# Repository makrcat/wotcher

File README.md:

## wotcher

wotcher is a digital raise-to-wake LED watch, with 89 LEDs in total! It uses something called charlieplexing to make all the lights glow at once. 

## circuit design
Charlieplexing is a method to limit current & control many LED's with only a couple of microcontroller pins, by switching between LEDs really fast so it looks like they're always on, due to the phenomenon of persistence of vision.

- My project uses a charlieplexing chip (IS31FL3731-QF) to drive the 7-segment display & all 60 LEDs, which is 88 LEDs in total. 
- The clock chip (DS3231MZ+) is necessary here because the ATtiny's internal RC oscillator clock is terrible at time keeping. The clock chip only drifts like 2 seconds a year! So that's cool.
- I'm also including an accelerometer so that it's raise-to-wake, like those Apple watches.

# some inspiration

It's inspired by various retro-style watches, such as the aptly named retrowatch, the charlie watch, and the decko circuit face watch, as well as other pinterest pictures.

<i>from left to right, <a src="https://trmm.net/Charliewatch/">charliewatch</a>, <a src="https://github.com/RafaelRiber/RetroWatch">retrowatch</a>, decko (by the Terminelectro company)</i>

## features

I'm going to use embedded c++ to code this later, when I get my breadboard components.

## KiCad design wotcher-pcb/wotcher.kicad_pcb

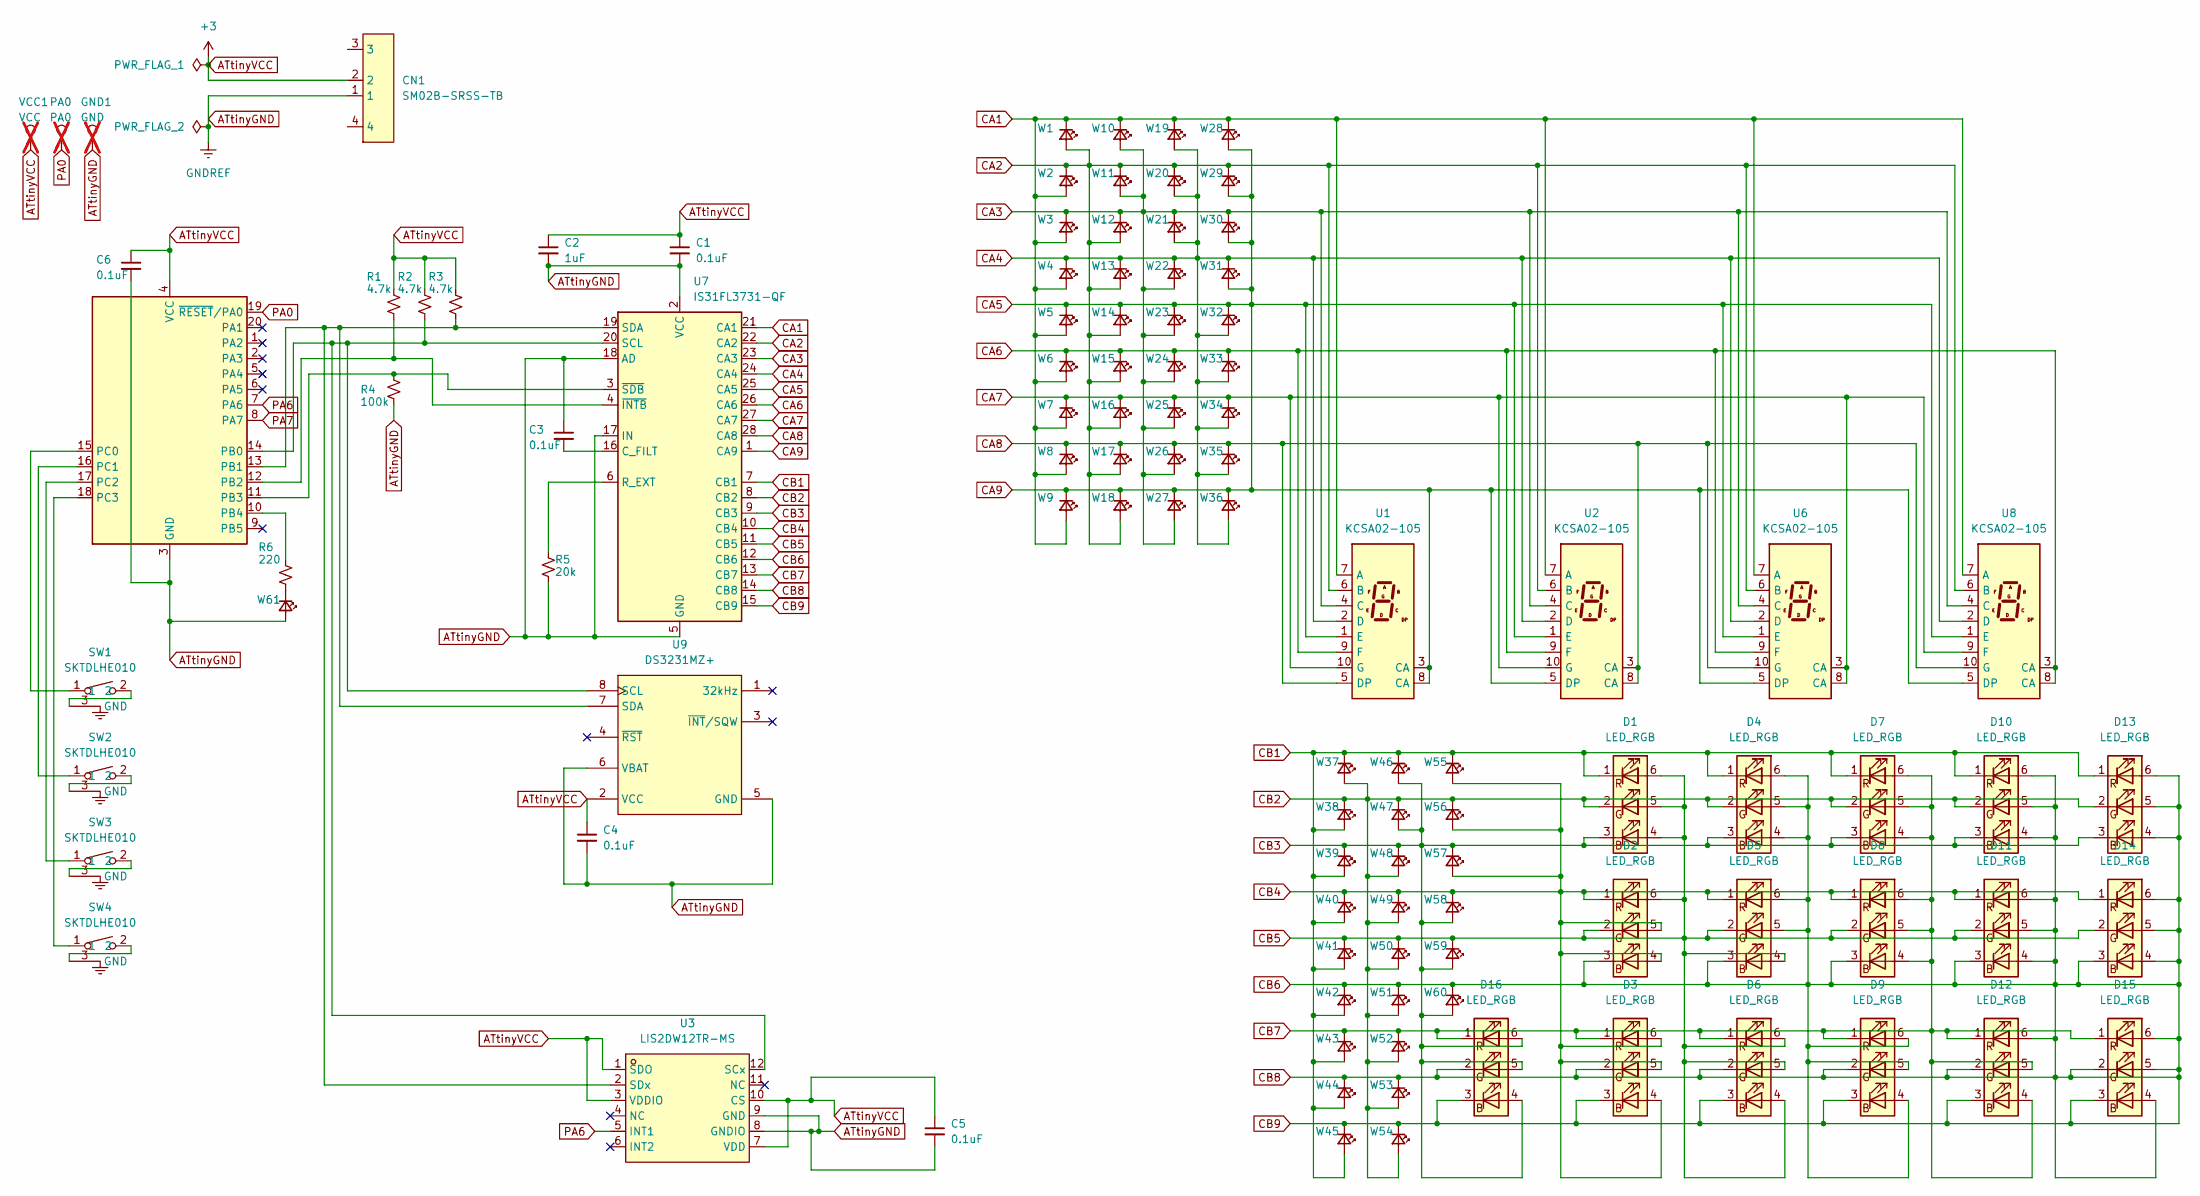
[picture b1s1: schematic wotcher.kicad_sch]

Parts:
C1, C3, C4, C5, C6: 0.1uF; C_01005_0402Metric
C2: 1uF; C_01005_0402Metric
CN1: SM02B-SRSS-TB; CONN-SMD_2P-P1.00_SM02B-SRSS-TB-LF-SN; MPN SM02B-SRSS-TB(LF)(SN); LCSC Part C160402
D1, D2, D3, D4, D5, D6, D7, D8, D9, D10, D11, D12, D13, D14, D15, D16: LED_RGB; LED-ARRAY-SMD_6P-L1.6-W1.6-TL_19-337C-RSBHGHC-M01
GND1: GND; TestPoint_Pad_D1.5mm; not fitted
PA0: PA0; TestPoint_Pad_D1.5mm; not fitted
R1, R2, R3: 4.7k; R_0201_0603Metric
R4: 100k; R_0201_0603Metric
R5: 20k; R_0201_0603Metric
R6: 220; R_0201_0603Metric
SW1, SW2, SW3, SW4: SKTDLHE010; KEY-SMD_SKTDLHE010; MPN SKTDLHE010; LCSC Part C380198
U1, U2, U6, U8: KCSA02-105; KCSC02-105
U3: LIS2DW12TR-MS; LGA-12_L2.0-W2.0_BMA250; MPN LIS2DW12TR-MS; LCSC Part C50385411
U5: ATtiny1616-M; QFN-20_L3.0-W3.0-P0.40-BL-EP1.7
U7: IS31FL3731-QF; QFN-28_L4.0-W4.0-P0.40-BL-EP
U9: DS3231MZ+; SOIC-8_L4.9-W3.9-P1.27-LS6.0-BL; MPN DS3231MZ+TRL; LCSC Part C107410
VCC1: VCC; TestPoint_Pad_D1.5mm; not fitted
W1, W2, W3, W4, W5, W6, W7, W8, W9, W10, W11, W12, W13, W14, W15, W16, W17, W18, W19, W20, W21, W22, W23, W24, W25, W26, W27, W28, W29, W30, W31, W32, W33, W34, W35, W36, W37, W38, W39, W40, W41, W42, W43, W44, W45, W46, W47, W48, W49, W50, W51, W52, W53, W54, W55, W56, W57, W58, W59, W60, W61: LED_Small; LED-SMD_L1.6-W0.8-R-RD

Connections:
ATtinyGND: C1.2, C2.2, C3.1, C4.2, C5.2, C6.2, CN1.1, GND1.1, R4.2, R5.2, U3.8 (GNDIO), U3.9 (GND), U5.3 (GND), U5.21 (GND), U7.2 (VCC), U7.5 (GND), U7.17 (IN), U7.18 (AD), U7.29 (GND), U9.5 (GND), U9.6 (VBAT), W61.2 (A)
ATtinyVCC: C1.1, C2.1, C4.1, C5.1, C6.1, CN1.2, R1.1, R2.1, R3.1, U3.1 (SDO), U3.3 (VDDIO), U3.7 (VDD), U3.10 (CS), U5.4 (VCC), U9.2 (VCC), VCC1.1
CA1: U1.7 (A), U2.7 (A), U6.7 (A), U7.21 (CA1), U8.7 (A), W1.1 (K), W2.2 (A), W3.2 (A), W4.2 (A), W5.2 (A), W6.2 (A), W7.2 (A), W8.2 (A), W9.2 (A), W10.1 (K), W19.1 (K), W28.1 (K)
CA2: U1.6 (B), U2.6 (B), U6.6 (B), U7.22 (CA2), U8.6 (B), W1.2 (A), W2.1 (K), W11.1 (K), W12.2 (A), W13.2 (A), W14.2 (A), W15.2 (A), W16.2 (A), W17.2 (A), W18.2 (A), W20.1 (K), W29.1 (K)
CA3: U1.4 (C), U2.4 (C), U6.4 (C), U7.23 (CA3), U8.4 (C), W3.1 (K), W10.2 (A), W11.2 (A), W12.1 (K), W21.1 (K), W22.2 (A), W23.2 (A), W24.2 (A), W25.2 (A), W26.2 (A), W27.2 (A), W30.1 (K)
CA4: U1.2 (D), U2.2 (D), U6.2 (D), U7.24 (CA4), U8.2 (D), W4.1 (K), W13.1 (K), W19.2 (A), W20.2 (A), W21.2 (A), W22.1 (K), W31.1 (K), W32.2 (A), W33.2 (A), W34.2 (A), W35.2 (A), W36.2 (A)
CA5: U1.1 (E), U1.3 (CA), U1.8 (CA), U2.1 (E), U2.5 (DP), U6.1 (E), U6.5 (DP), U7.1 (CA9), U7.25 (CA5), U8.1 (E), U8.5 (DP), W5.1 (K), W9.1 (K), W14.1 (K), W18.1 (K), W23.1 (K), W27.1 (K), W28.2 (A), W29.2 (A), W30.2 (A), W31.2 (A), W32.1 (K), W36.1 (K)
CA6: U1.9 (F), U2.9 (F), U6.9 (F), U7.26 (CA6), U8.3 (CA), U8.8 (CA), W6.1 (K), W15.1 (K), W24.1 (K), W33.1 (K)
CA7: U1.10 (G), U2.10 (G), U6.3 (CA), U6.8 (CA), U7.27 (CA7), U8.9 (F), W7.1 (K), W16.1 (K), W25.1 (K), W34.1 (K)
CA8: U1.5 (DP), U2.3 (CA), U2.8 (CA), U6.10 (G), U7.28 (CA8), U8.10 (G), W8.1 (K), W17.1 (K), W26.1 (K), W35.1 (K)
CB1: D1.1 (RK), D4.1 (RK), D7.1 (RK), D10.1 (RK), D13.1 (RK), U7.7 (CB1), W37.1 (K), W38.2 (A), W39.2 (A), W40.2 (A), W41.2 (A), W42.2 (A), W43.2 (A), W44.2 (A), W45.2 (A), W46.1 (K), W55.1 (K)
CB2: D1.2 (GK), D4.2 (GK), D7.2 (GK), D10.2 (GK), D13.2 (GK), U7.8 (CB2), W37.2 (A), W38.1 (K), W47.1 (K), W48.2 (A), W49.2 (A), W50.2 (A), W51.2 (A), W52.2 (A), W53.2 (A), W54.2 (A), W56.1 (K)
CB3: D1.3 (BK), D4.3 (BK), D7.3 (BK), D10.3 (BK), D13.3 (BK), D16.4 (BA), D16.5 (GA), D16.6 (RA), U7.9 (CB3), W39.1 (K), W46.2 (A), W47.2 (A), W48.1 (K), W57.1 (K), W58.2 (A), W59.2 (A), W60.2 (A)
CB4: D2.1 (RK), D2.4 (BA), D2.5 (GA), D3.4 (BA), D3.5 (GA), D3.6 (RA), D5.1 (RK), D8.1 (RK), D11.1 (RK), D14.1 (RK), U7.10 (CB4), W40.1 (K), W49.1 (K), W55.2 (A), W56.2 (A), W57.2 (A), W58.1 (K)
CB5: D1.4 (BA), D1.5 (GA), D1.6 (RA), D2.2 (GK), D2.6 (RA), D5.2 (GK), D5.4 (BA), D6.4 (BA), D6.5 (GA), D6.6 (RA), D8.2 (GK), D11.2 (GK), D14.2 (GK), U7.11 (CB5), W41.1 (K), W50.1 (K), W59.1 (K)
CB6: D2.3 (BK), D3.2 (GK), D3.3 (BK), D4.4 (BA), D4.5 (GA), D4.6 (RA), D5.3 (BK), D5.5 (GA), D5.6 (RA), D6.2 (GK), D6.3 (BK), D8.3 (BK), D9.2 (GK), D9.3 (BK), D9.4 (BA), D9.5 (GA), D9.6 (RA), D10.4 (BA), D10.5 (GA), D10.6 (RA), D11.3 (BK), D11.4 (BA), D11.5 (GA), D11.6 (RA), D12.2 (GK), D12.3 (BK), D12.6 (RA), D13.4 (BA), D13.5 (GA), D13.6 (RA), D14.3 (BK), D14.4 (BA), D14.5 (GA), D14.6 (RA), D15.2 (GK), D15.3 (BK), D15.4 (BA), D15.5 (GA), D15.6 (RA), D16.2 (GK), D16.3 (BK), U7.12 (CB6), U7.14 (CB8), U7.15 (CB9), W42.1 (K), W44.1 (K), W45.1 (K), W51.1 (K), W53.1 (K), W54.1 (K), W60.1 (K)
CB7: D3.1 (RK), D6.1 (RK), D7.4 (BA), D7.5 (GA), D7.6 (RA), D8.4 (BA), D8.5 (GA), D8.6 (RA), D9.1 (RK), D12.1 (RK), D12.4 (BA), D12.5 (GA), D15.1 (RK), D16.1 (RK), U7.13 (CB7), W43.1 (K), W52.1 (K)
unnamed: SW1.2, SW1.3 (GND)
unnamed: SW2.2, SW2.3 (GND)
unnamed: SW3.2, SW3.3 (GND)
unnamed: SW4.2, SW4.3 (GND)
unnamed: R2.2, U3.12 (SCx), U5.14 (PB0), U7.20 (SCL), U9.8 (SCL)
unnamed: R3.2, U3.2 (SDx), U5.13 (PB1), U7.19 (SDA), U9.7 (SDA)
unnamed: R1.2, U5.12 (PB2), U7.4 (~INTB)
unnamed: R4.1, U5.11 (PB3), U7.3 (~SDB)
unnamed: R6.1, U5.10 (PB4)
unnamed: SW1.1, U5.15 (PC0)
unnamed: SW2.1, U5.16 (PC1)
unnamed: SW3.1, U5.17 (PC2)
unnamed: SW4.1, U5.18 (PC3)
unnamed: C3.2, U7.16 (C_FILT)
unnamed: R5.1, U7.6 (R_EXT)
unnamed: R6.2, W61.1 (K)
PA0: PA0.1, U5.19 (~RESET/PA0)
PA6: U3.5 (INT1), U5.7 (PA6)
PA7: U5.8 (PA7)

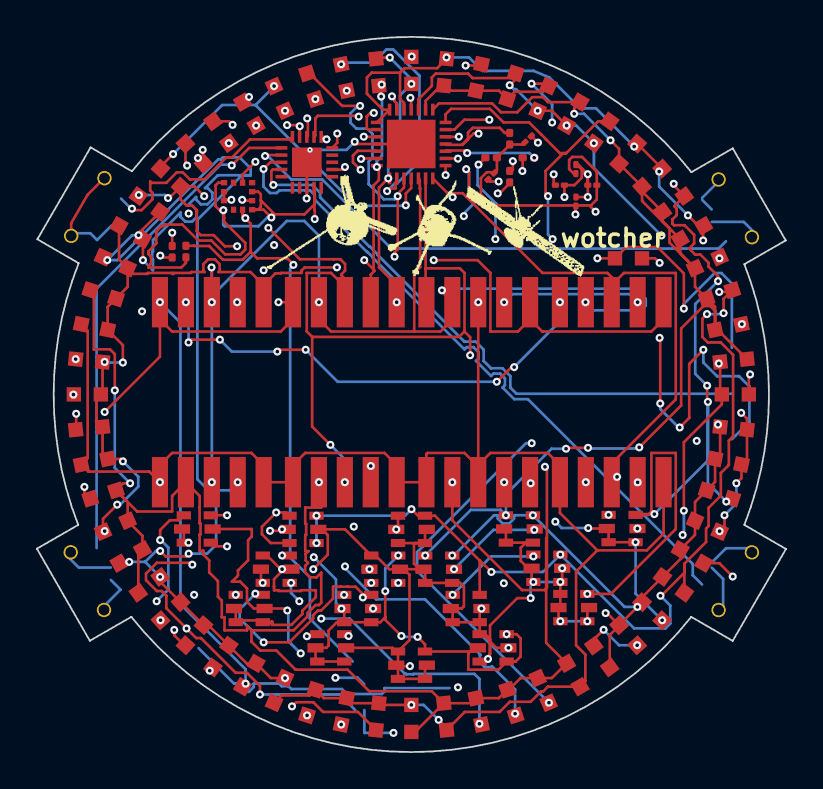
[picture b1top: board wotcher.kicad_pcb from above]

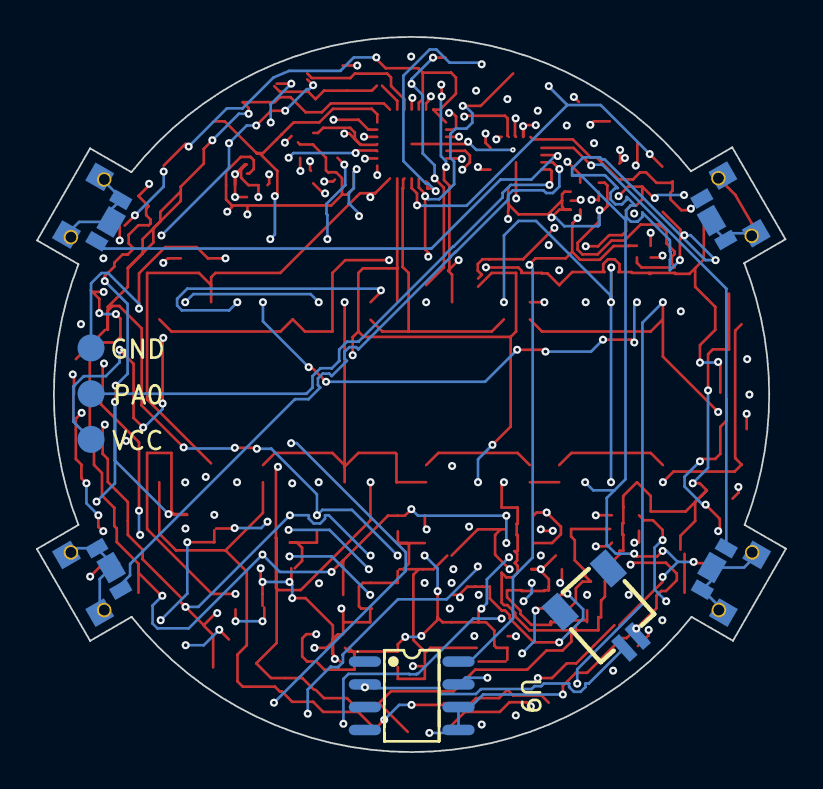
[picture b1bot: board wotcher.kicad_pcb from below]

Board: 4 copper layers, 41.6 x 39.7 mm, 105 parts (9 on the bottom side), 35 nets.

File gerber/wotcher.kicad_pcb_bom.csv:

Designator,Quantity,Value,Footprint,Package,MPN,DNP,Mount_Type,Description,LCSC Part,Manufacturer,Sim.Pins
"C1, C3, C4, C5, C6",5,0.1uF,C_01005_0402Metric,,,,smt,"Unpolarized capacitor, small symbol",,,
C2,1,1uF,C_01005_0402Metric,,,,smt,"Unpolarized capacitor, small symbol",,,
CN1,1,SM02B-SRSS-TB,CONN-SMD_2P-P1.00_SM02B-SRSS-TB-LF-SN,,SM02B-SRSS-TB(LF)(SN),,smt,,C160402,JST,
"D1, D10, D11, D12, D13, D14, D15, D16, D2, D3, D4, D5, D6, D7, D8, D9",16,LED_RGB,LED-ARRAY-SMD_6P-L1.6-W1.6-TL_19-337C-RSBHGHC-M01,,,,tht,"RGB LED, 6 pin package",,,
"R1, R2, R3",3,4.7k,R_0201_0603Metric,,,,smt,"Resistor, small US symbol",,,
R4,1,100k,R_0201_0603Metric,,,,smt,"Resistor, small US symbol",,,
R5,1,20k,R_0201_0603Metric,,,,smt,"Resistor, small US symbol",,,
R6,1,220,R_0201_0603Metric,,,,smt,"Resistor, small US symbol",,,
"SW1, SW2, SW3, SW4",4,SKTDLHE010,KEY-SMD_SKTDLHE010,,SKTDLHE010,,smt,,C380198,ALPSALPINE(阿尔卑斯阿尔派),
"U1, U2, U6, U8",4,KCSA02-105,KCSC02-105,,,,smt,"One digit 7 segment hyper red LED, common anode",,,
U3,1,LIS2DW12TR-MS,LGA-12_L2.0-W2.0_BMA250,,LIS2DW12TR-MS,,smt,,C50385411,MSKSEMI(美森科),
U5,1,ATtiny1616-M,VQFN-20-1EP_3x3mm_P0.4mm_EP1.7x1.7mm,,,,smt,"20MHz, 16kB Flash, 2kB SRAM, 256B EEPROM, VQFN-20",,,
U7,1,IS31FL3731-QF,QFN-28-1EP_4x4mm_P0.4mm_EP2.3x2.3mm,,,,smt,"9x16 LED matrix driver with 8-bit PWM and breathing, QFN-28",,,
U9,1,DS3231MZ+,SOIC-8_L4.9-W3.9-P1.27-LS6.0-BL,,DS3231MZ+TRL,,smt,,C107410,ADI(亚德诺)/MAXIM(美信),
"W1, W10, W11, W12, W13, W14, W15, W16, W17, W18, W19, W2, W20, W21, W22, W23, W24, W25, W26, W27, W28, W29, W3, W30, W31, W32, W33, W34, W35, W36, W37, W38, W39, W4, W40, W41, W42, W43, W44, W45, W46, W47, W48, W49, W5, W50, W51, W52, W53, W54, W55, W56, W57, W58, W59, W6, W60, W61, W7, W8, W9",61,LED_Small,LED-SMD_L1.6-W0.8-R-RD,,,,smt,"Light emitting diode, small symbol",C2286,,1=K 2=A
